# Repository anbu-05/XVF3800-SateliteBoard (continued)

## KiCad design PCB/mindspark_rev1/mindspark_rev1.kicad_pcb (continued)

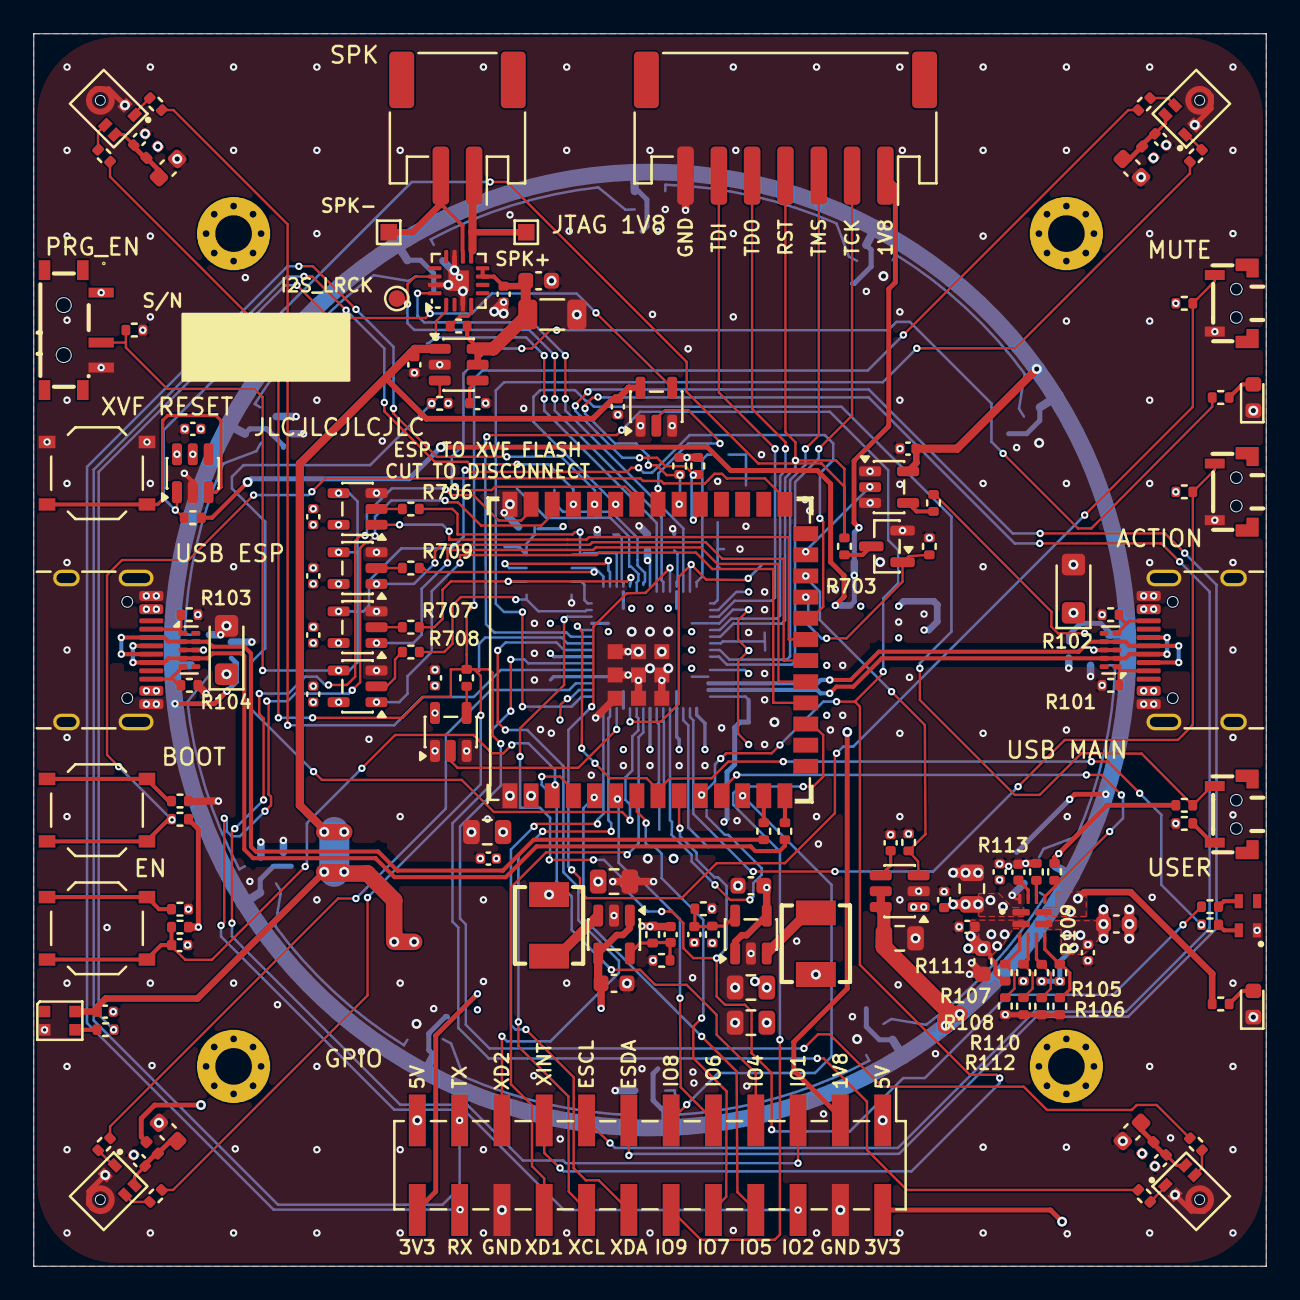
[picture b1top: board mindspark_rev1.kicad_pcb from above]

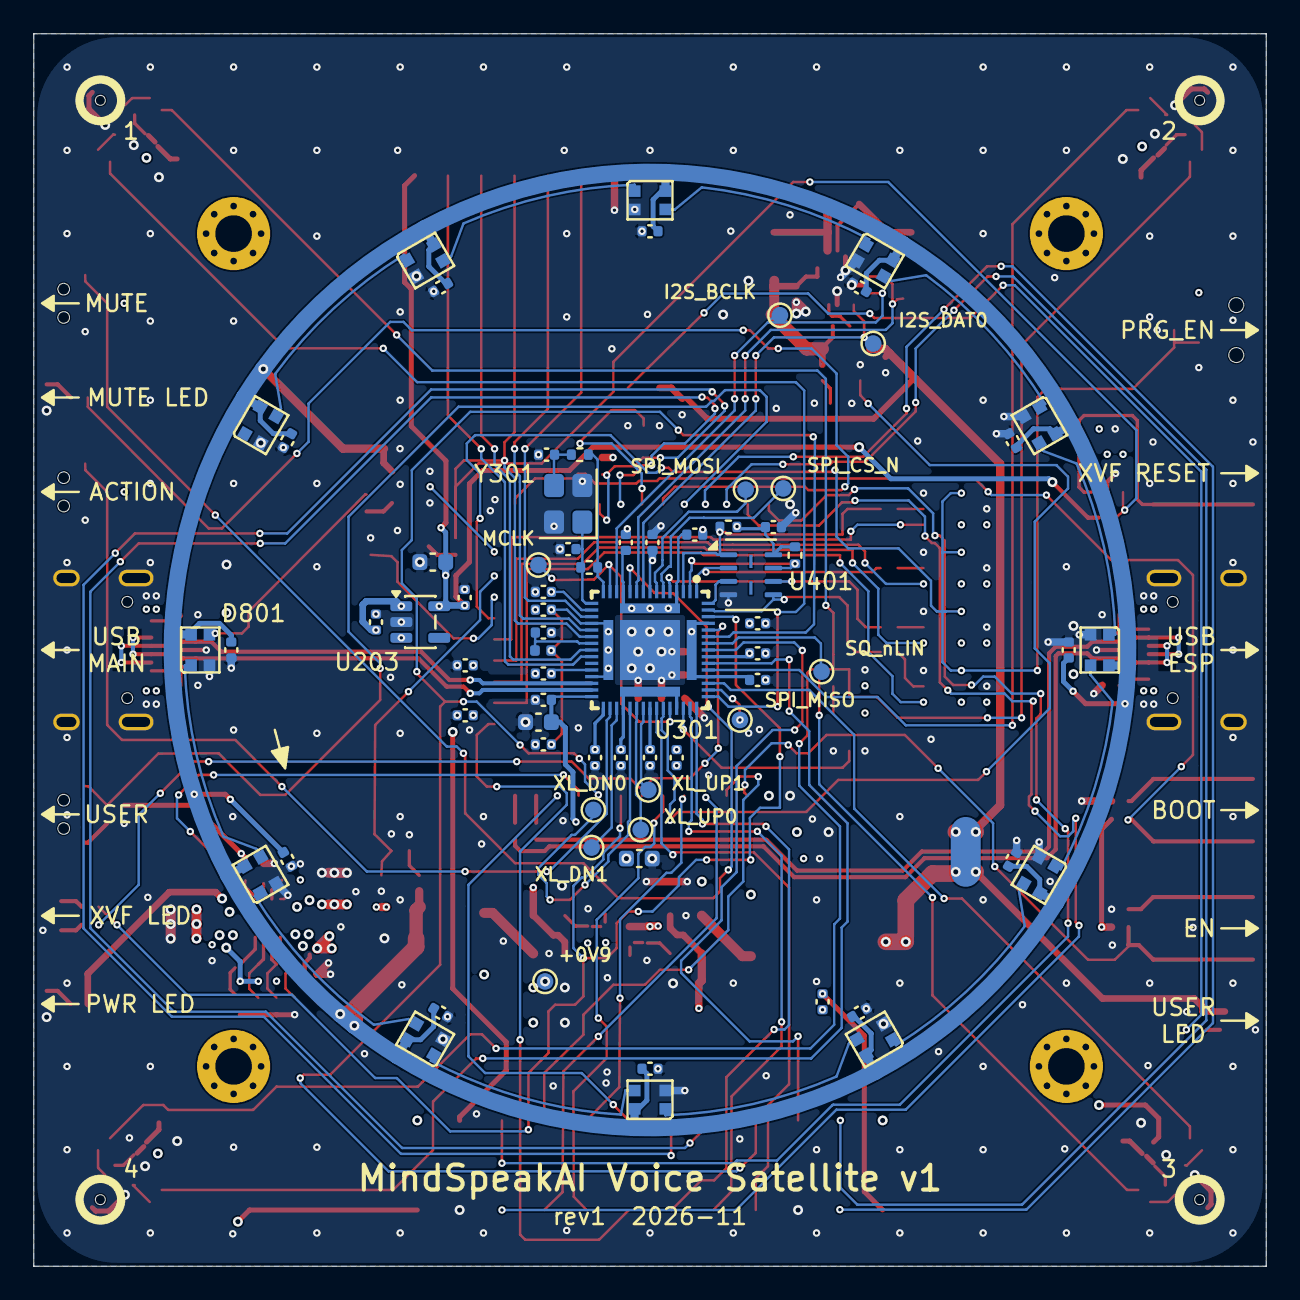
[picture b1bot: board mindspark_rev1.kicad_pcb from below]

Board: 4 copper layers, 74.0 x 74.0 mm, 223 parts (72 on the bottom side), 144 nets.

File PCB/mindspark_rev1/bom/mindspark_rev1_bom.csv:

"Designator","Value","Footprint","LCSC","MPN","Manufacturer","Voltage","Spec","Qty"
"C101,C103,C202,C206,C309,C314,C318,C506,C510,C512-C514","10uF","Mindspark:C_0603_1608Metric","C19702","CL10A106KP8NNNC","Samsung","","","12"
"C102,C104,C105,C107,C301-C308,C310-C313,C315-C317,C322,C325,C326,C401,C501,C509,C515,C602,C604,C605,C701-C704,C801-C812,C816","100nF","Mindspark:C_0402_1005Metric","C1525","CL05B104KO5NNNC","Samsung","","","46"
"C106,C203,C204,C207,C601,C815","22uF","Mindspark:C_0805_2012Metric","C45783","CL21A226MAQNNNE","Samsung","","","6"
"C201,C320,C321","22pF","Mindspark:C_0402_1005Metric","C1555","0402CG220J500NT","FH","","","3"
"C205","15pF","Mindspark:C_0402_1005Metric","C1548","0402CG150J500NT","FH","","","1"
"C208,C209,C319,C502-C505,C508,C603,C814","1uF","Mindspark:C_0402_1005Metric","C52923","CL05A105KA5NQNC","Samsung","","","10"
"C507,C813","1nF","Mindspark:C_0402_1005Metric","C1523","0402B102K500NT","FH","","","2"
"C511","47uF","Mindspark:C_1206_3216Metric","C96123","CL31A476MPHNNNE","Samsung","","","1"
"D101,D102","SMF5.0A","Mindspark:D_SMF","C193402","SMF5.0A","MDD","","","2"
"D201","GREEN","Mindspark:LED_0603_1608Metric","C12624","KT-0603G","Hubei KENTO","","","1"
"D401","RED","Mindspark:LED_0603_1608Metric","C2286","KT-0603R","Hubei KENTO","","","1"
"D402","RGB","Mindspark:LED_RGB_TOGIALED_1615_1.6x1.5mm","C601684","TJ-S1615CY6TGLCCSRGB-A5","TOGIALED","","","1"
"D601,D801-D812","WS2812B-2020","Mindspark:LED_WS2812B-2020_PLCC4_2.0x2.0mm","C52917434","WS2812B-2020-V6","Worldsemi","","","13"
"FB301,FB501-FB504","600R@100MHz","Mindspark:L_0402_1005Metric","C76884","BLM15AG601SN1D","Murata","","","5"
"J101,J102","TYPE-C-31-M-12","Mindspark:USB_C_Receptacle_HRO_TYPE-C-31-M-12","C165948","TYPE-C-31-M-12","Korean Hroparts","","","2"
"J301","S7B-PH-SM4-TB(LF)(SN)","Mindspark:JST_PH_S7B-PH-SM4-TB_1x07-1MP_P2.00mm_Horizontal","C265453","S7B-PH-SM4-TB(LF)(SN)","JST","","","1"
"J501","S2B-PH-SM4-TB(LF)(SN)","Mindspark:JST_PH_S2B-PH-SM4-TB_1x02-1MP_P2.00mm_Horizontal","C295747","S2B-PH-SM4-TB(LF)(SN)","JST","","","1"
"J701","GPIO","Mindspark:PinHeader_2x12_P2.54mm_Vertical_SMD_HCTL_PZ254","C3294470","PZ254-2-12-S","HCTL","","","1"
"L201,L202","2.2uH","Mindspark:L_Bourns_SRP4020TA","C719179","SRP4020TA-2R2M","Bourns","","","2"
"MK501-MK504","SPH0641LM4H-1","Mindspark:Knowles_SPH0641LM4H-1_LGA-5_3.5x2.65mm","C497724","SPH0641LM4H-1","Knowles","","","4"
"Q701","2N7002","Mindspark:SOT-23","C8545","2N7002","CJ (Changjiang)","","","1"
"R101-R104","5.1k","Mindspark:R_0402_1005Metric","C25905","0402WGF5101TCE","UNI-ROYAL","","","4"
"R105,R107,R204","22k","Mindspark:R_0402_1005Metric","C25768","0402WGF2202TCE","UNI-ROYAL","","","3"
"R106,R110,R112","12k","Mindspark:R_0402_1005Metric","C25752","0402WGF1202TCE","UNI-ROYAL","","","3"
"R108,R114,R303,R402,R403,R601,R602,R607","10k","Mindspark:R_0402_1005Metric","C25744","0402WGF1002TCE","UNI-ROYAL","","","8"
"R109,R111,R201","51k","Mindspark:R_0402_1005Metric","C25794","0402WGF5102TCE","UNI-ROYAL","","","3"
"R113","33k","Mindspark:R_0402_1005Metric","C25779","0402WGF3302TCE","UNI-ROYAL","","","1"
"R202,R203,R510","100k","Mindspark:R_0402_1005Metric","C25741","0402WGF1003TCE","UNI-ROYAL","","","3"
"R205","2.2k","Mindspark:R_0402_1005Metric","C25879","0402WGF2201TCE","UNI-ROYAL","","","1"
"R301","680R","Mindspark:R_0402_1005Metric","C25130","0402WGF6800TCE","UNI-ROYAL","","","1"
"R302,R511","1M","Mindspark:R_0402_1005Metric","C26083","0402WGF1004TCE","UNI-ROYAL","","","2"
"R401,R407,R701,R702,R704,R705,R801","4.7k","Mindspark:R_0402_1005Metric","C25900","0402WGF4701TCE","UNI-ROYAL","","","7"
"R404,R405,R603,R604,R609","1k","Mindspark:R_0402_1005Metric","C11702","0402WGF1001TCE","UNI-ROYAL","","","5"
"R406","330R","Mindspark:R_0402_1005Metric","C25104","0402WGF3300TCE","UNI-ROYAL","","","1"
"R501-R509","100R","Mindspark:R_0402_1005Metric","C25076","0402WGF1000TCE","UNI-ROYAL","","","9"
"R605,R606","27R","Mindspark:R_0402_1005Metric","C25100","0402WGF270JTCE","UNI-ROYAL","","","2"
"R608,R802","33R","Mindspark:R_0402_1005Metric","C25105","0402WGF330JTCE","UNI-ROYAL","","","2"
"R703,R706-R709","0R","Mindspark:R_0402_1005Metric","C17168","0402WGF0000TCE","UNI-ROYAL","","","5"
"SW301","RESET","Mindspark:SW_Push_1P1T_XKB_TS-1187A","C318884","TS-1187A-B-A-B","XKB Connection","","","1"
"SW401","MUTE","Mindspark:SW_SHOUHAN_TS24CA_SideActuated","C393942","TS24CA","SHOU HAN","","","1"
"SW402","ACTION","Mindspark:SW_SHOUHAN_TS24CA_SideActuated","C393942","TS24CA","SHOU HAN","","","1"
"SW601","EN","Mindspark:SW_Push_1P1T_XKB_TS-1187A","C318884","TS-1187A-B-A-B","XKB Connection","","","1"
"SW602","BOOT","Mindspark:SW_Push_1P1T_XKB_TS-1187A","C318884","TS-1187A-B-A-B","XKB Connection","","","1"
"SW603","USER","Mindspark:SW_SHOUHAN_TS24CA_SideActuated","C393942","TS24CA","SHOU HAN","","","1"
"SW701","PROG","Mindspark:SW_SHOUHAN_MSK12C02_SideActuated","C431540","MSK12C02","SHOU HAN","","","1"
"U101,U102","TPD4E05U06DQAR","Mindspark:USON-10_2.5x1.0mm_P0.5mm","C138714","TPD4E05U06DQAR","Texas Instruments","","","2"
"U103","TPS2121RUXR","Mindspark:TI_RUX0012A_VQFN-HR-12_2x2.5mm","C485916","TPS2121RUXR","Texas Instruments","","","1"
"U201,U202","TLV62569DBVR","Mindspark:SOT-23-5","C141836","TLV62569DBVR","Texas Instruments","","","2"
"U203","TLV75518PDBVR","Mindspark:SOT-23-5","C2877863","TLV75518PDBVR","Texas Instruments","","","1"
"U301","XVF3800-QF60B-C","Mindspark:XMOS_QFN-60-5EP_7x7mm_P0.4mm","C20491135","XVF3800-QF60B-C","XMOS","","","1"
"U302","TPS3808G33DBVR","Mindspark:SOT-23-6","C43698","TPS3808G33DBVR","Texas Instruments","","","1"
"U401","GD25Q16ENIGR","Mindspark:Winbond_USON-8-2EP_3x4mm_P0.8mm_EP0.2x0.8mm","C5749719","GD25Q16ENIGR","GigaDevice","","","1"
"U501","SN74LVC1G125DBVR","Mindspark:SOT-23-5","C23654","SN74LVC1G125DBVR","Texas Instruments","","","1"
"U502,U801","TPS22918DBVR","Mindspark:SOT-23-6","C131941","TPS22918DBVR","Texas Instruments","","","2"
"U503","MAX98357AETE+T","Mindspark:TQFN-16-1EP_3x3mm_P0.5mm_EP1.23x1.23mm","C910544","MAX98357AETE+T","Analog Devices (Maxim)","","","1"
"U601","ESP32-S3-WROOM-1U-N16R8","Mindspark:ESP32-S3-WROOM-1U","C3013946","ESP32-S3-WROOM-1U-N16R8","Espressif","","","1"
"U602,U802","SN74AHCT1G125DBVR","Mindspark:SOT-23-5","C7484","SN74AHCT1G125DBVR","Texas Instruments","","","2"
"U701-U704","TS5A3166DBVR","Mindspark:SOT-23-5","C353035","TS5A3166DBVR","Texas Instruments","","","4"
"Y301","24MHz","Mindspark:Crystal_SMD_3225-4Pin_3.2x2.5mm","C70590","X322524MOB4SI","YXC","","","1"

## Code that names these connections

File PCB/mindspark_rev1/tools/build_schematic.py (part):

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        "59": "XVF_QSPI_D0", "60": "XVF_QSPI_D2", "61": V9, "62": V9, "63": V9, "64": V9, "65": "GND"},
        prefix="U", join=(("61", "62", "63", "64"),),
        fields=dict(spec="Voice processor", use="XMOS XVF3800, stock USB firmware"))
    # MIC_CLK (pin 43) leaves unterminated: as on XMOS's XK-VOICE-SQ66, the buffer and the
    # series resistors sit with the mics (sheet audio).

    g = s.group("Decoupling and PLL filter")
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    # Parallel pads wired to the header lines (one pad per pin, in pin order).
    pads_on_lines(g, j, [(p, jt[p]) for p in "1234567"], -22.86, ["JTAG%s" % p for p in "1234567"],
                  "Mindspark:TestPoint_Pad_1.0x1.0mm", ["JTAG parallel pad %s" % p for p in "1234567"])  # 1.0 mm: user's KiCad edit 2026-11-12
    s.exceptions.append("MCLK_LOOP: labelled between pins 14 and 41 (opposite sides of U301)")
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    s.note("Decoupling per XU316: >= 8 x 100 nF on VDD, 100 nF per VDDIO pin, >= 10 uF per rail; PLL_AVDD via 600 R ferrite + 1 uF. Crystal on the 1.8 V bank.")
    s.note("USB D+/D- go straight to the main USB-C (ESD on sheet usb_power); bus-powered, no VBUS sense.")
    return s

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    g = s.group("Mute and status LEDs")
    led = g.part("LED", 0, 10.16, {"1": "GND", "2": "LED_MUTE_A"}, rot=90, prefix="D", value="RED", attach=("2",),
                 fields=dict(spec="0603 red", use="Mute indicator"), footprint="Mindspark:LED_0603_1608Metric")
    g.inline(led["2"][0], (0, -1), "R", "ESP_MUTE_LED", "1k", n_near="LED_MUTE_A", use="Mute LED from ESP32 GPIO41, about 1.3 mA")
    rgb = g.part("TJ-S1615CY6TGLCCSRGB-A5", 25.4, 7.62, {"4": "LED_RGB_R", "3": "LED_RGB_G", "2": None, "1": "GND"},
                 prefix="D", value="RGB", attach=("3", "4"),
                 fields=dict(spec="RGB, common cathode", use="XVF3800 status, red pin 56, green pin 58; blue unused"))
    for pin, net, an, val in (("4", "XVF_GPO_R", "LED_RGB_R", "1k"), ("3", "XVF_GPO_G", "LED_RGB_G", "330R")):
        (px, py), d = rgb[pin]
        g.inline((px, py), d, "R", net, val, n_near=an, use="RGB status LED series resistor",
                 fieldpos=[("Reference", nref(g, "R"), px + 2.54 + 3.81, py - 1.6, "center", 0.9),
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               fieldpos=[("Reference", nref(g, "J"), jx - 5.08, -6.0, "left"),
                         ("Value", "S2B-PH-SM4-TB", jx - 5.08, 9.5, "left"), ("spec", "JST PH 2-pin, 2 A", jx - 5.08, 11.0, "left", 0.9)])
    xt = 27.94
    for pin, net, rot, value, use, fy in (("9", "SPK_P", 0, "SPK+", "Speaker solder pad +", -4.3),
                                          ("10", "SPK_N", 180, "SPK-", "Speaker solder pad -", 4.3)):
        (ax, ay), _ = u[pin]
        g.wire((ax + 2.54, ay), j["1" if net == "SPK_P" else "2"][0])
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    "ESP_UART_TX": "output", "ESP_UART_RX": "input", "ESP_I2C_SDA": "bidirectional", "ESP_I2C_SCL": "bidirectional",
    "PRG_CS_N": "output", "PRG_CLK": "output", "PRG_DI": "output", "PRG_DO": "input",
    "PRG_RST": "output", "PRG_EN": "input",
    "ESP_GPIO1": "bidirectional", "ESP_GPIO2": "bidirectional", "ESP_GPIO4": "bidirectional",
    "ESP_GPIO5": "bidirectional", "ESP_GPIO6": "bidirectional", "ESP_GPIO7": "bidirectional",
    "ESP_GPIO8": "bidirectional", "ESP_GPIO9": "bidirectional",
}
# Module pad -> net (GPIO in the comment). Strapping pins 3, 45, 46 and the PSRAM pins 35-37 are
# left unconnected; GPIO0 keeps only the BOOT pull-up and button. SPI2 (FSPI) uses its IO_MUX
# pins 10-13 for path B. GPIO19/20 are the USB pins.
ESP_PINS = {
    "1": "GND", "40": "GND", "41": "GND", "2": "+3V3", "3": "ESP_EN", "27": "ESP_BOOT",       # GPIO0
    "39": "ESP_GPIO1", "38": "ESP_GPIO2", "4": "ESP_GPIO4", "5": "ESP_GPIO5",                 # 1, 2, 4, 5
    "6": "ESP_GPIO6", "7": "ESP_GPIO7", "12": "ESP_GPIO8", "17": "ESP_GPIO9",                 # 6, 7, 8, 9
    "18": "PRG_CS_N", "19": "PRG_DI", "20": "PRG_CLK", "21": "PRG_DO",                        # 10 CS, 11 MOSI, 12 CLK, 13 MISO
    "22": "PRG_EN", "23": "PRG_RST",                                                          # 14, 21
    "8": "XVF_GPO_R", "9": "XVF_GPO_G", "10": "XVF_INT_N", "11": "MUX_ST",                    # 15, 16, 17, 18
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    g.junction(n1)
    g.junction(n2)
    nb = (bx, -12.7)
    vbranch(g, "R", (bx, -15.24), (0, -1), "ESP_BOOT", "+3V3", "10k", use="GPIO0 pull-up (Espressif)",
            fieldpos=[("Reference", nref(g, "R"), bx + 1.8, -19.82, "left", 1.0), ("Value", "10k", bx + 1.8, -18.32, "left", 1.0)])
    g.wire(nb, (bx, -15.24))
    g.wire(nb, (bx + 2.54, -12.7))
    g.anchor((bx + 2.54, -12.7), (1, 0), "ESP_BOOT")
    g.junction(nb)
    for i, (net, name, use) in enumerate((("ESP_EN", "EN", "ESP32 reset (EN) button"),
                                          ("ESP_BOOT", "BOOT", "ESP32 BOOT (GPIO0) button"))):
        x = (ex, bx)[i]
        sw = g.part("TS-1187A-B-A-B", x, -5.08, {"1": net, "2": net + "_R"}, rot=270, prefix="SW", value=name,
                    attach=("1", "2"), fields=dict(use=use),
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        g.wire(sw["1"][0], (x, -12.7))
        g.inline(sw["2"][0], (0, 1), "R", "GND", "1k", n_near=net + "_R", use="%s button series resistor" % name,
                 fieldpos=[("Reference", nref(g, "R"), x + 2.3, 6.86, "left", 1.0), ("Value", "1k", x + 2.3, 8.36, "left", 1.0)])
    s.exceptions.append("ESP_EN / ESP_BOOT: labelled between the button circuits and the module's dense pins")

    g = s.group("USB series resistors")
    g.R(0, 0, "ESP_USB_DP", "USB_ESP_DP", "27R", orient="h", use="USB D+ series (Espressif: 22-33 R)")
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        "PRG_RST": "input", "XVF_RST_N": "bidirectional", "PRG_EN": "output",
        "ESP_UART_TX": "input", "ESP_UART_RX": "output",
        "ESP_I2C_SDA": "bidirectional", "ESP_I2C_SCL": "bidirectional",
        "ESP_GPIO1": "bidirectional", "ESP_GPIO2": "bidirectional", "ESP_GPIO4": "bidirectional",
        "ESP_GPIO5": "bidirectional", "ESP_GPIO6": "bidirectional", "ESP_GPIO7": "bidirectional",
        "ESP_GPIO8": "bidirectional", "ESP_GPIO9": "bidirectional",
        "XVF_I2C_SCL": "bidirectional", "XVF_I2C_SDA": "bidirectional", "XVF_INT_N": "input",
        "XVF_I2S_DATA1": "bidirectional", "XVF_I2S_DATA2": "bidirectional"},
        "Switch-enabled flash switches (path B), XVF3800 reset, I2C pull-ups and 2x12 GPIO header")
    g = s.group("XVF flash switches (U701-U704)")
    pairs = (("XVF_QSPI_CS_N", "PRG_CS_N"), ("XVF_QSPI_CLK", "PRG_CLK"),
             ("XVF_QSPI_D0", "PRG_DI"), ("XVF_QSPI_D1", "PRG_DO"))
    # The four IN pins share one PRG_EN wire: each IN line runs left under its COM label to a
    # riser per column; the risers meet along the bottom. One port label on the left riser.
    XL, XR, YB = -29.21, 26.67, 58.42
    ins = []
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        r.C("+3V3", "GND", "100nF", "10V", use="Switch bypass, U%d" % (701 + i))

    g = s.group("PROG switch, XVF reset")
    # Side slide switch (replaces the JP701 jumper, 2026-11-11). The common pin drives PRG_EN:
    # slid to pin 1 = +3V3 (programming), to pin 3 = GND (normal run). The 4.7k pull-down keeps
    # PRG_EN low while the slider is between positions.
    sw = g.part("MSK12C02", 0, 0, {"1": "+3V3", "2": "PRG_EN", "3": "GND"}, prefix="SW", value="PROG", attach=("2",),
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    g = s.group("GPIO header (J701, 2x12)")
    # Pin 13-14 and 15-16 put the two I2C buses side by side: two jumper shunts join them.
    g.part("Conn_02x12_Odd_Even", 0, 0, {
        "1": "+5V", "2": "+3V3", "3": "+1V8", "4": "GND", "5": "ESP_GPIO1", "6": "ESP_GPIO2",
        "7": "ESP_GPIO4", "8": "ESP_GPIO5", "9": "ESP_GPIO6", "10": "ESP_GPIO7", "11": "ESP_GPIO8",
        "12": "ESP_GPIO9", "13": "ESP_I2C_SDA", "14": "XVF_I2C_SDA", "15": "ESP_I2C_SCL", "16": "XVF_I2C_SCL",
        "17": "XVF_INT_N", "18": "XVF_I2S_DATA1", "19": "XVF_I2S_DATA2", "20": "GND",
        "21": "ESP_UART_TX", "22": "ESP_UART_RX", "23": "+5V", "24": "+3V3"},
        prefix="J", value="GPIO", footprint="Mindspark:PinHeader_2x12_P2.54mm_Vertical_SMD_HCTL_PZ254",
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    r = Row(g, 33.02, -5.08)
    r.C("+5V_LED", "GND", "100nF", "16V", spec="X7R", use="Buffer bypass")

    s.note("The buffer runs from the switched rail, so the ESP32 must hold LED_DATA low while LED_EN is off. Data from ESP32 GPIO48 (RMT).")
    return s


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
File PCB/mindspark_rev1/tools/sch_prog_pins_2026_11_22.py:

"""Shift the ESP32's flash-programming pins (user, 2026-11-22).

The four PRG lines leave ESP32 pins 18-21 (GPIO10-13) on the east side of the module and run to
the flash switches west of it (tools/prog_switch_route_2026_11_22.py). With the old order the line
for the top switch (PRG_CS_N) came out at the bottom and had to loop round the others. New order,
so the lines leave in the order of the switch column (top to bottom CS_N, DO, CLK, DI):

    pin 21  GPIO13  PRG_CS_N   (was PRG_DO)
    pin 20  GPIO12  PRG_DO     (was PRG_CLK)
    pin 19  GPIO11  PRG_CLK    (was PRG_DI)
    pin 18  GPIO10  PRG_DI     (was PRG_CS_N)

SPI2 now goes through the GPIO matrix instead of its IOMUX pins; fine at flash-programming speed.
Edits esp32.kicad_sch (the four hierarchical labels and the GPIO note) and the board's pad nets for
U601 pads 18-21.

Usage (schematic and PCB editors closed):  python3 tools/sch_prog_pins_2026_11_22.py
"""
import os
import sys

sys.path.insert(0, os.path.dirname(__file__))
from place_tidy import BOARD, Part  # noqa: E402
from sexpr import parse, dump, children, child, q  # noqa: E402

HERE = os.path.join(os.path.dirname(__file__), "..")
SHEET = os.path.join(HERE, "esp32.kicad_sch")
BY_Y = {68.58: "PRG_DI", 71.12: "PRG_CLK", 73.66: "PRG_DO", 76.2: "PRG_CS_N"}   # GPIO10..13 rows
OLD = {68.58: "PRG_CS_N", 71.12: "PRG_DI", 73.66: "PRG_CLK", 76.2: "PRG_DO"}
PADS = {"18": "/PRG_DI", "19": "/PRG_CLK", "20": "/PRG_DO", "21": "/PRG_CS_N"}
NOTE_OLD = "10-13 SPI2 to the XVF flash (CS, MOSI=DI, CLK, MISO=DO)"
NOTE_NEW = "10-13 SPI2 (GPIO matrix) to the XVF flash (10 MOSI=DI, 11 CLK, 12 MISO=DO, 13 CS)"

s = parse(open(SHEET).read())
done = 0
for h in children(s, "hierarchical_label"):
    at = child(h, "at")
    y = round(float(at[2]), 2)
    if abs(float(at[1]) - 31.75) < 0.01 and y in BY_Y:
        if str(h[1]) != OLD[y]:
            sys.exit(f"label at y {y} is {h[1]}, expected {OLD[y]}: nothing done")
        h[1] = q(BY_Y[y])
        done += 1
if done != 4:
    sys.exit(f"found {done} of 4 labels: nothing written")
for t in children(s, "text"):
    if NOTE_OLD in str(t[1]):
        t[1] = q(str(t[1]).replace(NOTE_OLD, NOTE_NEW))
open(SHEET, "w").write(dump(s) + "\n")
print("relabelled GPIO10-13:", ", ".join(BY_Y.values()))

b = parse(open(BOARD).read())
for f in children(b, "footprint"):
    if Part(f).ref == "U601":
        for pd in children(f, "pad"):
            if str(pd[1]) in PADS:
                child(pd, "net")[1] = q(PADS[str(pd[1])])
open(BOARD, "w").write(dump(b) + "\n")
print("U601 pads 18-21 renamed on the board")

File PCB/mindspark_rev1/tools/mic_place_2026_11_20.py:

"""Placement for the mic routes (approved by the user 2026-11-20).

  1. C312 0.2 mm north and C307 0.2 mm south: the gap between them grows from 0.6 to 1.0 mm so
     MIC_DATA3 and MIC_DATA1 (pins 51/50) pass straight between them at the pin pitch.
  2. C309 (10 uF, XVF3800 +0V9 bulk) leaves the fan-out west of the chip. It goes to the spot
     the clock buffer frees between the bucks, on the In2 +0V9 neck: its +0V9 pad sits over the
     neck (via in pad), its GND pad just west of it.
  3. Clock buffer group U501 / R501 / C501 moves to the top side, just west of the ESP32 module.
     The clock star (R501 pad 2) then runs on F.Cu over solid In1 GND, where no data line runs.
     U501 input (pin 2) faces south, where MIC_CLK arrives from XVF3800 pin 43; output (pin 4)
     faces north-east with R501 above it; C501 above pin 5 (+3V3).
  4. New footprint C515 (stitching cap +3V3 / +5V, from tools/sch_mic_stitch_2026_11_20.py), a
     copy of C501 on the bottom side, just east of the SE mic pair where it crosses from the
     In2 +3V3 plane to +5V (y 119.8; the pair runs at x 134.7 / 135.15 there, 2.5 mm clear of L202):
     +3V3 pad north of the edge, +5V pad south of it.

Tracks, vias and zones are left to tools/power_v2_2026_11_18.py and tools/mic_route_2026_11_20.py.
Usage (PCB editor closed):  python3 tools/mic_place_2026_11_20.py [--dry-run]
"""
import copy
import sys
import uuid

sys.path.insert(0, __import__("os").path.dirname(__file__))
from place_tidy import BOARD, Part, overlap  # noqa: E402
from sexpr import parse, dump, children, child, walk, q  # noqa: E402

SHEET = "/3f22dfb6-6fd6-54c4-9781-a982d7ddf190"          # audio sheet (as in C501's path)
C515_SYM = str(uuid.uuid5(uuid.NAMESPACE_URL, "mindspark_rev1/audio/C515"))
C515_POSE = (136.2, 119.8, 90.0)                           # checked below: pad 1 (+3V3) north

MOVES = {  # ref: (x, y, rotation)
    "C312": (140.098, 98.879, 180.0),
    "C307": (140.098, 100.479, 180.0),
    "C309": (147.2, 111.2, 180.0),
}
TO_TOP = {  # ref: (x, y, rotation) after flipping to the top side
    "U501": (134.6, 103.6, None),
    "R501": (135.55, 100.35, None),
    "C501": (133.65, 100.35, None),
}

root = parse(open(BOARD).read())
P = {}
for f in children(root, "footprint"):
    p = Part(f)
    P[p.ref] = p
if "C515" in P:
    sys.exit("C515 already on the board: nothing to do")


def prop(node, name):
    for p in children(node, "property"):
        if p[1] == name:
            return p
    return None


def pad_centres(ref):
    out = {}
    for pd, poly in zip(children(P[ref].node, "pad"), P[ref].pads()):
        xs, ys = [a for a, _ in poly], [b for _, b in poly]
        out[str(pd[1])] = ((min(xs) + max(xs)) / 2, (min(ys) + max(ys)) / 2)
    return out


# 4 (made first). stitching cap: a copy of C501 while C501 is still on the bottom side
f = copy.deepcopy(P["C501"].node)
for u in walk(f, "uuid"):
    u[1] = q(str(uuid.uuid4()))
child(f, "path")[1] = q(f"{SHEET}/{C515_SYM}")
prop(f, "Reference")[2] = q("C515")
prop(f, "use")[2] = q("Mic stitching: +3V3/+5V where the SE mic pair crosses planes (In2)")
for pd in children(f, "pad"):
    child(pd, "net")[1] = q("+3V3" if str(pd[1]) == "1" else "+5V")
root.insert(root.index(P["C501"].node) + 1, f)
P["C515"] = Part(f)

# 1-2. bottom-side moves
for ref, pose in MOVES.items():
    P[ref].place(*pose)

# 3. clock buffer group to the top side. Rotation is picked so the pins land where wanted:
#    U501 pin 2 south of the body, pin 4 north-east; R501 pad 1 south (to pin 4); C501 pad 1
#    south (+3V3, beside pin 5).
WANT = {"U501": lambda c: c["2"][1] > TO_TOP["U501"][1] and c["4"][1] < TO_TOP["U501"][1]
        and c["4"][0] > TO_TOP["U501"][0],
        "R501": lambda c: c["1"][1] > c["2"][1],
        "C501": lambda c: c["1"][1] > c["2"][1]}
for ref, (x, y, _) in TO_TOP.items():
    P[ref].flip_to_top()
    for rot in (0.0, 90.0, 180.0, -90.0):
        P[ref].place(x, y, rot)
        if WANT[ref](pad_centres(ref)):
            break
    else:
        sys.exit(f"no rotation puts {ref}'s pins where wanted")

# 4. stitching cap: placed above, from C501 while it was still on the bottom side
for rot in (90.0, -90.0):
    P["C515"].place(C515_POSE[0], C515_POSE[1], rot)
    c = pad_centres("C515")
    if c["1"][1] < c["2"][1]:
        break


def shapes(ref):
    p = P[ref]
    return ([p.courtyard()] if p.local_box("CrtYd") else []) + p.pads()


clash = []
for g in list(MOVES) + list(TO_TOP) + ["C515"]:
    for ref, p in P.items():
        if ref == g:
            continue
        if p.side != P[g].side and not ref.startswith(("J10", "H", "SW", "MK")):
            continue
        other = shapes(ref) if p.side == P[g].side else p.pads(only_th=True)
        if any(overlap(s, o) for s in shapes(g) for o in other):
            clash.append("/".join(sorted((g, ref))))
print("overlaps:", sorted(set(clash)) or "none")
for ref in list(MOVES) + list(TO_TOP) + ["C515"]:
    print(f"  {ref} {P[ref].side} " + " ".join(f"{k}:({v[0]:.3f},{v[1]:.3f})" for k, v in sorted(pad_centres(ref).items())))
if "--dry-run" not in sys.argv:
    open(BOARD, "w").write(dump(root) + "\n")
    print("wrote", BOARD)

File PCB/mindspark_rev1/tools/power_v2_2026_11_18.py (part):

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    ("GND", "In1.Cu", 0, [(LEFT, TOP), (RIGHT, TOP), (RIGHT, BOTTOM), (LEFT, BOTTOM)]),
    ("+3V3", "In2.Cu", 0, [(LEFT, TOP), (RIGHT, TOP), (RIGHT, BOTTOM), (LEFT, BOTTOM)]),
    # +5V: since 2026-11-19 a finger east of the arm (x 170.7-173.3, y 112.9-114.9) into what was
    # VBUS_MAIN, for the U103 pin-8 vias east of the LED ring
    ("+5V", "In2.Cu", 1, [(152.3, 109.8), (170.7, 109.8), (170.7, 112.9), (173.3, 112.9), (173.3, 114.9),
                          (170.7, 114.9), (170.7, 114.75), (164.3, 114.75), (164.3, 130.2),
                          (130.5, 130.2), (130.5, 115.5), (134.3, 115.5), (134.3, 119.8), (146.2, 119.8),
                          (146.2, 122.0), (158.9, 122.0), (158.9, 113.4), (152.3, 113.4)]),
    # VBUS_MAIN: notched for that finger; the strip below it (y 115.25-117.2) takes the pin-7 vias.
    # Since 2026-11-23 (tools/plane_necks_2026_11_23.py) the west edge runs at x 170.8 down to
    # y 108.3 and back to x 172.8 at 45 degrees, round the row of LED-ring crossing vias.
    ("VBUS_MAIN", "In2.Cu", 2, [(170.8, 94.8), (178.6, 94.8), (178.6, 117.2), (171.0, 117.2), (171.0, 115.25),
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                               (164.6, 130.5), (164.6, 115.05), (170.7, 115.05), (170.7, 134.9), (114.6, 134.9)]),
    ("+0V9", "In2.Cu", 4, [(142.3, 94.4), (149.45, 94.4), (149.45, 103.0), (148.8, 103.0), (148.8, 113.7),
                           (158.8, 113.7), (158.8, 121.7), (147.0, 121.7), (147.0, 103.0),
                           # lobe under C306 (2026-11-22): its pin 42 is fenced in by the MIC_CLK and
                           # MCLK vias, so the cap takes a via in its pad into the island instead;
                           # wide above y 104 so the fill flows round those two vias' clearance, narrow
                           # below so C311's +3V3 via keeps its plane
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VIA_3V3_FB503 = (119.6, 126.0)
# +3V3 for J701 pin 2 (breakout header, east end; 2026-11-20): it used to join FB504's +3V3 feed,
# which the SE mic pair's F.Cu legs now cut off. In2 under J701 is +5V / VBUS_ESP; the nearest
# +3V3 plane is east of the VBUS_ESP strip (x > 170.7): one via there, F.Cu west to the pin.
VIA_3V3_J701 = (171.3, 133.0)
for pt, net in ((VIA_5V_A, "+5V"), (VIA_5V_B, "+5V"), (VIA_1V8_S, "+1V8"),
                (HOP1, "+1V8"), (HOP2, "+1V8"), (VIA_3V3_FB503, "+3V3"), (VIA_3V3_J701, "+3V3")):
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# wrong In2 plane, and the B.Cu LED ring runs under the chip's east half. Each pin gets a small
# F.Cu pour (solid to the pad) out to its own group of 0.6/0.3 vias (1 A each), in its own plane:
#   pin 1 +5V       1.5 A: 2 vias west, the pour also takes in C106's +5V pad (the 3 A bulk cap)
#   pin 2 VBUS_ESP  3 A:   3 vias south-west, the pour also takes in C104 and C103's VBUS_ESP pads
#   pin 7 VBUS_MAIN 3 A:   3 vias east (In2 strip below the +5V finger), with C102 and C101's pads
#   pin 8 +5V       1.5 A: 2 vias north-east, past the ring, in the In2 +5V finger
# The spots were checked by hand against the ring, D812, the pins' signal escapes (pins 3-6 go
# south to the dividers, 9-12 north) and the In2 plane edges; DRC confirms. The pours keep 0.2 mm
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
